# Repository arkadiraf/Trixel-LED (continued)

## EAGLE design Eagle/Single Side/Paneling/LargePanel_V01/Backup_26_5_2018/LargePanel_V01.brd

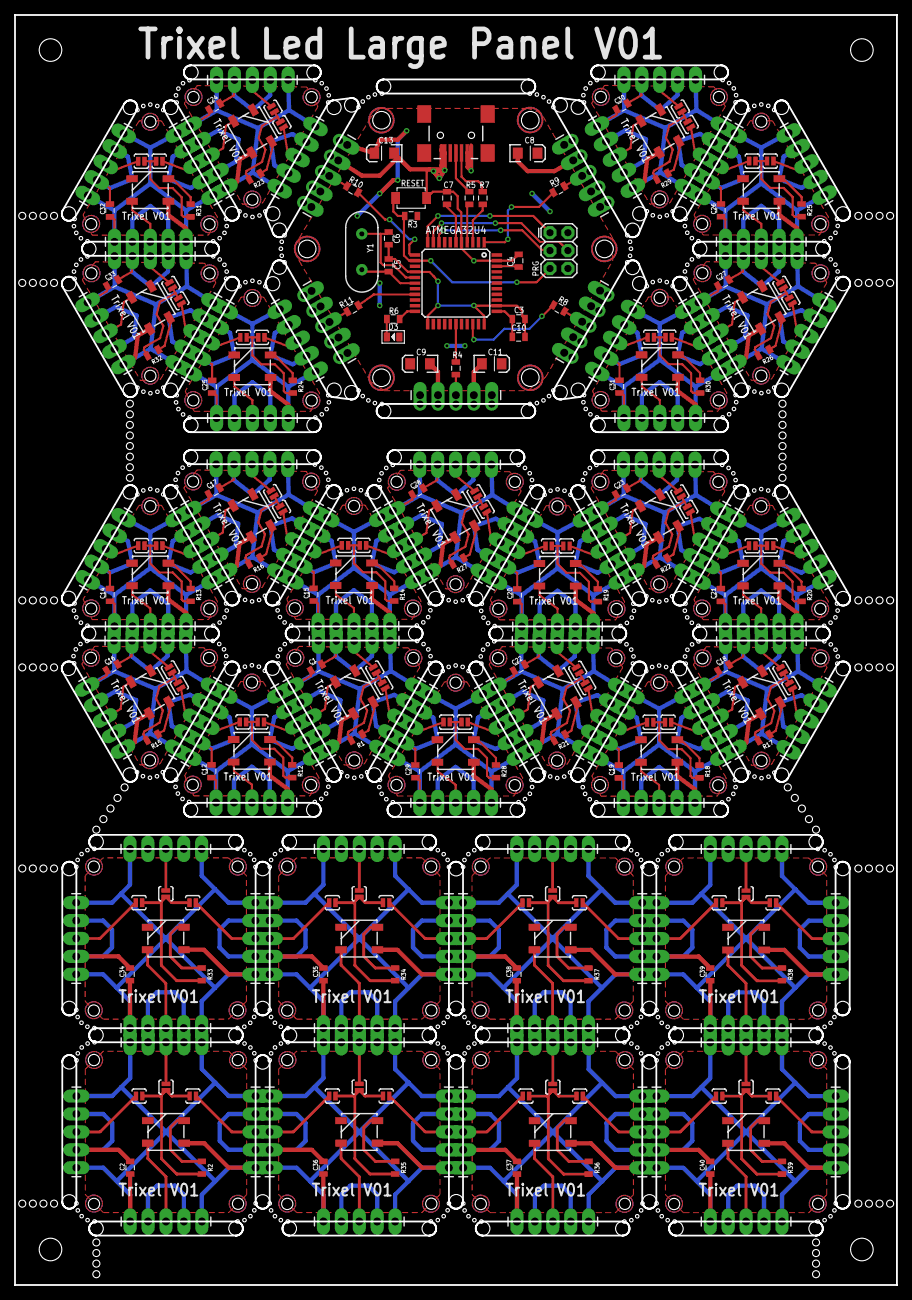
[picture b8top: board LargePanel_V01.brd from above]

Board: 2 copper layers, 125.0 x 180.0 mm, 291 parts (0 on the bottom side), 244 nets.

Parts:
ATMEGA32U4: ATMEGA32U4TQFP-44; TQFP44
C1, C2, C3, C4, C12, C14, C15, C16, C17, C18, C19, C20, C21, C22, C23, C24, C25, C26, C27, C28, C29, C30, C31, C32, C33, C34, C35, C36, C37, C38, C39, C40: 0.1uF; 0805
C5, C6: 22pF; 0805
C7, C10: 1uF; 0805
C8, C9, C11, C13: 10uF; EIA3216
D1, D2, D4, D5, D6, D7, D8, D9, D10, D11, D12, D13, D14, D15, D16, D17, D18, D19, D20, D21, D22, D23, D24, D25, D26, D27, D28, D29, D30, D31: WS2812B
D3: GREEN-0805; LED-0805
J1, J2, J4, J5, J6, J7, J8, J10, J12, J14, J16, J18, J19, J20, J21, J22, J23, J24, J25, J26, J27, J28, J29, J30, J31, J32, J33, J34, J35, J36, J37, J38, J39, J40, J41, J42, J43, J44, J45, J46, J47, J48, J49, J50, J51, J52, J53, J54, J55, J56, J57, J58, J59, J60, J61, J62, J63, J64, J65, J66, J67, J68, J69, J70, J71, J72, J73, J74, J75, J76, J77, J78, J79, J80, J81, J82, J83, J84, J85, J86, J87, J88, J89, J90, J91, J92, J93, J94, J95, J96, J97, J98, J99, J100, J101, J102, J103, J104, J105, J106, J107, J108, J109: 1X05_LONGPADS
J3: USB-MINIB-5PIN; USB-MINIB
J9, J11, J13, J15, J17: 1X05_NO_SILK
JP1, JP2, JP3, JP4, JP5, JP6, JP7, JP8, JP9, JP10, JP11, JP12, JP13, JP14, JP15, JP16, JP17, JP18, JP19, JP20, JP21, JP22, JP23, JP24, JP25, JP26, JP27, JP28, JP29, JP30, JP31, JP32, JP33, JP34, JP35, JP36, JP37, JP38, JP39, JP40, JP41, JP42, JP43, JP44, JP45, JP46, JP47, JP48, JP49, JP50, JP51, JP52, JP53, JP54, JP55, JP56, JP57, JP58, JP59, JP60, JP61, JP62, JP63, JP64, JP65, JP66, JP67, JP68: JUMPER-PAD-2-NOYES_SILK; PAD-JUMPER-2-NO_YES_SILK
PRG: AVR_SPI_PRG_6PTH; 2X3
R1, R4, R6, R8, R9, R10, R11, R12, R13, R14, R15, R16, R17, R18, R19, R20, R21, R22, R23, R24, R25, R26, R27, R28, R29, R30, R31, R32: 1k; 0805
R2, R33, R34, R35, R36, R37, R38, R39: 0805
R3: 10K; 0805
R5, R7: 22; 0805
RESET: B3U-1000P-2P-SMD; SW2-4.0X3.0X2.0
Y1: 16MHz; HC49US

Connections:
5V: ATMEGA32U4.2, ATMEGA32U4.7, ATMEGA32U4.14, ATMEGA32U4.24, ATMEGA32U4.34, ATMEGA32U4.44, C3.2, C8.A, C9.A, C10.1, C11.A, C13.A, D3.+, J3.VBUS, J9.1, J9.5, J10.1, J10.5, J11.1, J11.5, J12.1, J12.5, J13.1, J13.5, J14.1, J14.5, J15.1, J15.5, J16.1, J16.5, J17.1, J17.5, J18.1, J18.5, PRG.2, R3.2
AREF: ATMEGA32U4.42, C4.2
D2_SDA: ATMEGA32U4.19, R11.1
D5: ATMEGA32U4.31, R8.1
D7: ATMEGA32U4.1, R9.1
D8: ATMEGA32U4.28, R4.1
D11: ATMEGA32U4.12, R10.1
D+: ATMEGA32U4.4, R5.1
D-: ATMEGA32U4.3, R7.1
DIN: D1.4, J4.3
DIN1: D2.4, J8.3
DIN2: D4.4, J19.3
DIN3: D5.4, J22.3
DIN4: D6.4, J25.3
DIN5: D7.4, J28.3
DIN6: D8.4, J31.3
DIN7: D9.4, J34.3
DIN8: D10.4, J37.3
DIN9: D11.4, J40.3
DIN10: D12.4, J43.3
DIN11: D13.4, J46.3
DIN12: D14.4, J49.3
DIN13: D15.4, J52.3
DIN14: D16.4, J55.3
DIN15: D17.4, J58.3
DIN16: D18.4, J61.3
DIN17: D19.4, J64.3
DIN18: D20.4, J67.3
DIN19: D21.4, J70.3
DIN20: D22.4, J73.3
DIN21: D23.4, J76.3
DIN22: D24.4, J79.3
DIN23: D25.4, J85.3
DIN24: D26.4, J89.3
DIN25: D27.4, J93.3
DIN26: D28.4, J97.3
DIN27: D29.4, J101.3
DIN28: D30.4, J105.3
DIN29: D31.4, J109.3
DOUT: JP1.1, JP2.1, R1.2
DOUT1: JP3.1, JP4.1, JP5.1, R2.2
DOUT2: JP6.1, JP7.1, R12.2
DOUT3: JP8.1, JP9.1, R13.2
DOUT4: JP10.1, JP11.1, R14.2
DOUT5: JP12.1, JP13.1, R15.2
DOUT6: JP14.1, JP15.1, R16.2
DOUT7: JP16.1, JP17.1, R17.2
DOUT8: JP18.1, JP19.1, R18.2
DOUT9: JP20.1, JP21.1, R19.2
DOUT10: JP22.1, JP23.1, R20.2
DOUT11: JP24.1, JP25.1, R21.2
DOUT12: JP26.1, JP27.1, R22.2
DOUT13: JP28.1, JP29.1, R23.2
DOUT14: JP30.1, JP31.1, R24.2
DOUT15: JP32.1, JP33.1, R25.2
DOUT16: JP34.1, JP35.1, R26.2
DOUT17: JP36.1, JP37.1, R27.2
DOUT18: JP38.1, JP39.1, R28.2
DOUT19: JP40.1, JP41.1, R29.2
DOUT20: JP42.1, JP43.1, R30.2
DOUT21: JP44.1, JP45.1, R31.2
DOUT22: JP46.1, JP47.1, R32.2
DOUT23: JP48.1, JP49.1, JP50.1, R33.2
DOUT24: JP51.1, JP52.1, JP53.1, R34.2
DOUT25: JP54.1, JP55.1, JP56.1, R35.2
DOUT26: JP57.1, JP58.1, JP59.1, R36.2
DOUT27: JP60.1, JP61.1, JP62.1, R37.2
DOUT28: JP63.1, JP64.1, JP65.1, R38.2
DOUT29: JP66.1, JP67.1, JP68.1, R39.2
GND: C1.1, D1.3, J1.2, J1.4, J2.2, J2.4, J4.2, J4.4
GND1: C2.1, D2.3, J5.2, J5.4, J6.2, J6.4, J7.2, J7.4, J8.2, J8.4
GND2: ATMEGA32U4.5, ATMEGA32U4.15, ATMEGA32U4.23, ATMEGA32U4.33, ATMEGA32U4.35, ATMEGA32U4.43, C3.1, C4.1, C5.2, C6.2, C7.1, C8.C, C9.C, C10.2, C11.C, C13.C, J3.GND, J9.2, J9.4, J10.2, J10.4, J11.2, J11.4, J12.2, J12.4, J13.2, J13.4, J14.2, J14.4, J15.2, J15.4, J16.2, J16.4, J17.2, J17.4, J18.2, J18.4, PRG.6, RESET.1
GND3: C12.1, D4.3, J19.2, J19.4, J20.2, J20.4, J21.2, J21.4
GND4: C14.1, D5.3, J22.2, J22.4, J23.2, J23.4, J24.2, J24.4
GND5: C15.1, D6.3, J25.2, J25.4, J26.2, J26.4, J27.2, J27.4
GND6: C16.1, D7.3, J28.2, J28.4, J29.2, J29.4, J30.2, J30.4
GND7: C17.1, D8.3, J31.2, J31.4, J32.2, J32.4, J33.2, J33.4
GND8: C18.1, D9.3, J34.2, J34.4, J35.2, J35.4, J36.2, J36.4
GND9: C19.1, D10.3, J37.2, J37.4, J38.2, J38.4, J39.2, J39.4
GND10: C20.1, D11.3, J40.2, J40.4, J41.2, J41.4, J42.2, J42.4
GND11: C21.1, D12.3, J43.2, J43.4, J44.2, J44.4, J45.2, J45.4
GND12: C22.1, D13.3, J46.2, J46.4, J47.2, J47.4, J48.2, J48.4
GND13: C23.1, D14.3, J49.2, J49.4, J50.2, J50.4, J51.2, J51.4
GND14: C24.1, D15.3, J52.2, J52.4, J53.2, J53.4, J54.2, J54.4
GND15: C25.1, D16.3, J55.2, J55.4, J56.2, J56.4, J57.2, J57.4
GND16: C26.1, D17.3, J58.2, J58.4, J59.2, J59.4, J60.2, J60.4
GND17: C27.1, D18.3, J61.2, J61.4, J62.2, J62.4, J63.2, J63.4
GND18: C28.1, D19.3, J64.2, J64.4, J65.2, J65.4, J66.2, J66.4
GND19: C29.1, D20.3, J67.2, J67.4, J68.2, J68.4, J69.2, J69.4
GND20: C30.1, D21.3, J70.2, J70.4, J71.2, J71.4, J72.2, J72.4
GND21: C31.1, D22.3, J73.2, J73.4, J74.2, J74.4, J75.2, J75.4
GND22: C32.1, D23.3, J76.2, J76.4, J77.2, J77.4, J78.2, J78.4
GND23: C33.1, D24.3, J79.2, J79.4, J80.2, J80.4, J81.2, J81.4
GND24: C34.1, D25.3, J82.2, J82.4, J83.2, J83.4, J84.2, J84.4, J85.2, J85.4
GND25: C35.1, D26.3, J86.2, J86.4, J87.2, J87.4, J88.2, J88.4, J89.2, J89.4
GND26: C36.1, D27.3, J90.2, J90.4, J91.2, J91.4, J92.2, J92.4, J93.2, J93.4
GND27: C37.1, D28.3, J94.2, J94.4, J95.2, J95.4, J96.2, J96.4, J97.2, J97.4
GND28: C38.1, D29.3, J98.2, J98.4, J99.2, J99.4, J100.2, J100.4, J101.2, J101.4
GND29: C39.1, D30.3, J102.2, J102.4, J103.2, J103.4, J104.2, J104.4, J105.2, J105.4
GND30: C40.1, D31.3, J106.2, J106.4, J107.2, J107.4, J108.2, J108.4, J109.2, J109.4
MISO: ATMEGA32U4.11, PRG.1
MOSI: ATMEGA32U4.10, PRG.4
unnamed: J1.3, JP2.2
unnamed: J2.3, JP1.2
unnamed: D1.2, R1.1
unnamed: J7.3, JP4.2
unnamed: J6.3, JP3.2
unnamed: J5.3, JP5.2
unnamed: D2.2, R2.1
unnamed: ATMEGA32U4.16, C6.1, Y1.1
unnamed: ATMEGA32U4.17, C5.1, Y1.2
unnamed: J3.D-, R7.2
unnamed: J3.D+, R5.2
unnamed: D3.-, R6.2
unnamed: J9.3, J10.3, R4.2
unnamed: J11.3, J12.3, R8.2
unnamed: J13.3, J14.3, R9.2
unnamed: J15.3, J16.3, R10.2
unnamed: J17.3, J18.3, R11.2
unnamed: J20.3, JP7.2
unnamed: D4.2, R12.1
unnamed: J21.3, JP6.2
unnamed: J23.3, JP9.2
unnamed: D5.2, R13.1
unnamed: J24.3, JP8.2
unnamed: J26.3, JP11.2
unnamed: D6.2, R14.1
unnamed: J27.3, JP10.2
unnamed: J29.3, JP13.2
unnamed: D7.2, R15.1
unnamed: J30.3, JP12.2
unnamed: J32.3, JP15.2
unnamed: D8.2, R16.1
unnamed: J33.3, JP14.2
unnamed: J35.3, JP17.2
unnamed: D9.2, R17.1
unnamed: J36.3, JP16.2
unnamed: J38.3, JP19.2
unnamed: D10.2, R18.1
unnamed: J39.3, JP18.2
unnamed: J41.3, JP21.2
unnamed: D11.2, R19.1
unnamed: J42.3, JP20.2
unnamed: J44.3, JP23.2
unnamed: D12.2, R20.1
unnamed: J45.3, JP22.2
unnamed: J47.3, JP25.2
unnamed: D13.2, R21.1
unnamed: J48.3, JP24.2
unnamed: J50.3, JP27.2
unnamed: D14.2, R22.1
unnamed: J51.3, JP26.2
unnamed: J53.3, JP29.2
unnamed: D15.2, R23.1
unnamed: J54.3, JP28.2
unnamed: J56.3, JP31.2
unnamed: D16.2, R24.1
unnamed: J57.3, JP30.2
unnamed: J59.3, JP33.2
unnamed: D17.2, R25.1
unnamed: J60.3, JP32.2
unnamed: J62.3, JP35.2
unnamed: D18.2, R26.1
unnamed: J63.3, JP34.2
unnamed: J65.3, JP37.2
unnamed: D19.2, R27.1
unnamed: J66.3, JP36.2
unnamed: J68.3, JP39.2
unnamed: D20.2, R28.1
unnamed: J69.3, JP38.2
unnamed: J71.3, JP41.2
unnamed: D21.2, R29.1
unnamed: J72.3, JP40.2
unnamed: J74.3, JP43.2
unnamed: D22.2, R30.1
unnamed: J75.3, JP42.2
unnamed: J77.3, JP45.2
unnamed: D23.2, R31.1
unnamed: J78.3, JP44.2
unnamed: J80.3, JP47.2
unnamed: D24.2, R32.1
unnamed: J81.3, JP46.2
unnamed: J84.3, JP49.2
unnamed: J83.3, JP48.2
unnamed: J82.3, JP50.2
unnamed: D25.2, R33.1
unnamed: J88.3, JP52.2
unnamed: J87.3, JP51.2
unnamed: J86.3, JP53.2
unnamed: D26.2, R34.1
unnamed: J92.3, JP55.2
unnamed: J91.3, JP54.2
unnamed: J90.3, JP56.2
unnamed: D27.2, R35.1
unnamed: J96.3, JP58.2
unnamed: J95.3, JP57.2
unnamed: J94.3, JP59.2
unnamed: D28.2, R36.1
unnamed: J100.3, JP61.2
unnamed: J99.3, JP60.2
unnamed: J98.3, JP62.2
unnamed: D29.2, R37.1
unnamed: J104.3, JP64.2
unnamed: J103.3, JP63.2
unnamed: J102.3, JP65.2
unnamed: D30.2, R38.1
unnamed: J108.3, JP67.2
unnamed: J107.3, JP66.2
unnamed: J106.3, JP68.2
unnamed: D31.2, R39.1
RESET: ATMEGA32U4.13, PRG.5, R3.1, RESET.2
SCK: ATMEGA32U4.9, PRG.3
TXLED: ATMEGA32U4.22, R6.1
UCAP: ATMEGA32U4.6, C7.2
VIN: C1.2, D1.1, J1.1, J1.5, J2.1, J2.5, J4.1, J4.5
VIN1: C2.2, D2.1, J5.1, J5.5, J6.1, J6.5, J7.1, J7.5, J8.1, J8.5
VIN2: C12.2, D4.1, J19.1, J19.5, J20.1, J20.5, J21.1, J21.5
VIN3: C14.2, D5.1, J22.1, J22.5, J23.1, J23.5, J24.1, J24.5
VIN4: C15.2, D6.1, J25.1, J25.5, J26.1, J26.5, J27.1, J27.5
VIN5: C16.2, D7.1, J28.1, J28.5, J29.1, J29.5, J30.1, J30.5
VIN6: C17.2, D8.1, J31.1, J31.5, J32.1, J32.5, J33.1, J33.5
VIN7: C18.2, D9.1, J34.1, J34.5, J35.1, J35.5, J36.1, J36.5
VIN8: C19.2, D10.1, J37.1, J37.5, J38.1, J38.5, J39.1, J39.5
VIN9: C20.2, D11.1, J40.1, J40.5, J41.1, J41.5, J42.1, J42.5
VIN10: C21.2, D12.1, J43.1, J43.5, J44.1, J44.5, J45.1, J45.5
VIN11: C22.2, D13.1, J46.1, J46.5, J47.1, J47.5, J48.1, J48.5
VIN12: C23.2, D14.1, J49.1, J49.5, J50.1, J50.5, J51.1, J51.5
VIN13: C24.2, D15.1, J52.1, J52.5, J53.1, J53.5, J54.1, J54.5
VIN14: C25.2, D16.1, J55.1, J55.5, J56.1, J56.5, J57.1, J57.5
VIN15: C26.2, D17.1, J58.1, J58.5, J59.1, J59.5, J60.1, J60.5
VIN16: C27.2, D18.1, J61.1, J61.5, J62.1, J62.5, J63.1, J63.5
VIN17: C28.2, D19.1, J64.1, J64.5, J65.1, J65.5, J66.1, J66.5
VIN18: C29.2, D20.1, J67.1, J67.5, J68.1, J68.5, J69.1, J69.5
VIN19: C30.2, D21.1, J70.1, J70.5, J71.1, J71.5, J72.1, J72.5
VIN20: C31.2, D22.1, J73.1, J73.5, J74.1, J74.5, J75.1, J75.5
VIN21: C32.2, D23.1, J76.1, J76.5, J77.1, J77.5, J78.1, J78.5
VIN22: C33.2, D24.1, J79.1, J79.5, J80.1, J80.5, J81.1, J81.5
VIN23: C34.2, D25.1, J82.1, J82.5, J83.1, J83.5, J84.1, J84.5, J85.1, J85.5
VIN24: C35.2, D26.1, J86.1, J86.5, J87.1, J87.5, J88.1, J88.5, J89.1, J89.5
VIN25: C36.2, D27.1, J90.1, J90.5, J91.1, J91.5, J92.1, J92.5, J93.1, J93.5
VIN26: C37.2, D28.1, J94.1, J94.5, J95.1, J95.5, J96.1, J96.5, J97.1, J97.5
VIN27: C38.2, D29.1, J98.1, J98.5, J99.1, J99.5, J100.1, J100.5, J101.1, J101.5
VIN28: C39.2, D30.1, J102.1, J102.5, J103.1, J103.5, J104.1, J104.5, J105.1, J105.5
VIN29: C40.2, D31.1, J106.1, J106.5, J107.1, J107.5, J108.1, J108.5, J109.1, J109.5

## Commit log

2017-03-26 First commit
    Eagle design files uploaded
2018-04-11 Added sample code to hexagon mcu
2018-04-12 Panel updated
2018-05-25 Latest versions update
2018-07-26 Latest large panel designes
